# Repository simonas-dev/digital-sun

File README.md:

# Digital Sun

A cross-platform LED pattern system with real-time visualization and hardware control for Raspberry Pi.

## Overview

Digital Sun is a modular system for creating and displaying LED patterns:
- **Develop on macOS** with real-time OPENRNDR visualization
- **Deploy to Raspberry Pi** for physical LED strip control
- **Share core logic** between visualization and hardware

The build system automatically detects your platform and includes only relevant modules.

## Quick Start

### On macOS (Development & Visualization)
```bash
./gradlew build
./gradlew :sun-openrndr:run
```

### On Raspberry Pi (Hardware Control)
```bash
# Install rpi_ws281x library first (see BUILD.md)
./gradlew build
sudo ./target-rpi/build/bin/linuxArm64/releaseExecutable/target-rpi.kexe
```

## Project Structure

This project is organized into three modules:

### sun-core
Pure Kotlin/Java logic with no platform-specific dependencies.

**Contains:**
- `core/data/` - Data structures (Pixel, Stage)
- `core/shader/` - Shader algorithms and interfaces
- `core/noise/` - Noise generation interfaces

**Dependencies:** Kotlin stdlib, Kotlinx serialization, coroutines

**Purpose:** Reusable algorithms that can be used by any rendering backend.

### sun-openrndr
OPENRNDR visualization layer for desktop development and preview.

**Contains:**
- `openrndr/render/` - OPENRNDR-specific rendering
- `openrndr/noise/` - OPENRNDR noise adapter
- `openrndr/ui/` - GUI parameter controls
- Main application entry point

**Dependencies:** sun-core + OPENRNDR libraries

**Purpose:** Desktop application for developing and previewing shaders with a live GUI.

### target-rpi
Kotlin/Native LED strip control for Raspberry Pi via rpi_ws281x.

**Contains:**
- `rpi/` - Kotlin wrapper API for rpi_ws281x
- `nativeInterop/cinterop/` - C bindings for rpi_ws281x
- Example programs and animations

**Dependencies:** sun-core + rpi_ws281x (C library)

**Purpose:** Direct hardware control of WS281x LED strips on Raspberry Pi.

## Platform-Specific Builds

The build system automatically detects your platform:
- **macOS**: Builds `sun-core` + `sun-openrndr` (visualization)
- **Raspberry Pi** (Linux ARM): Builds `sun-core` + `target-rpi` (hardware)
- **Linux x86**: Builds all modules for testing

See [BUILD.md](BUILD.md) for detailed build instructions.

## Building

### macOS
```bash
./gradlew build                    # Builds sun-core + sun-openrndr
./gradlew :sun-openrndr:run        # Run visualization
./gradlew :sun-openrndr:shadowJar  # Create distributable
```

### Raspberry Pi
```bash
# Prerequisites: Install rpi_ws281x library (see BUILD.md)
./gradlew build                                        # Builds sun-core + target-rpi
./gradlew :target-rpi:linkReleaseExecutableLinuxArm64 # Build LED executable
sudo ./target-rpi/build/bin/linuxArm64/releaseExecutable/target-rpi.kexe
```

## Module Dependencies

```
┌──────────────────────┐          ┌──────────────────────┐
│    target-rpi        │          │    sun-openrndr      │
│  (Raspberry Pi HW)   │          │  (macOS/Linux viz)   │
│  Kotlin/Native       │          │  Kotlin/JVM          │
└──────────┬───────────┘          └──────────┬───────────┘
           │                                 │
           │         depends on              │
           └────────────┬────────────────────┘
                        │
                ┌───────▼────────┐
                │    sun-core    │
                │ (Shared logic) │
                │   Kotlin/JVM   │
                └────────────────┘
```

## Architecture

The core pattern logic is platform-agnostic. Different rendering backends provide:
1. **Noise generator implementation** - Adapts noise functions to the core interface
2. **Color output** - Converts core ColorValue to platform-specific format
3. **Rendering loop** - Drives patterns with time and parameters

This allows the same pattern logic to run on:
- **Desktop** (OPENRNDR) - Real-time preview with GUI controls
- **Raspberry Pi** (rpi_ws281x) - Physical LED strips via GPIO

## Documentation

- [BUILD.md](BUILD.md) - Detailed build instructions for all platforms
- [target-rpi/README.md](target-rpi/README.md) - LED hardware setup and API

## Requirements

- **All platforms**: JDK 17+, Gradle 8.14+ (included via wrapper)
- **Raspberry Pi only**: rpi_ws281x library (see BUILD.md for installation)

## License

MIT

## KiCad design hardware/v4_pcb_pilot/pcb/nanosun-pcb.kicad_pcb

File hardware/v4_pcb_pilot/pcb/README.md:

# nanosun-pcb

Carrier PCB for the SunsetLamp 150 mm circular LED pixel display. Holds 24 rows of WS2812B strip, provides power distribution and data routing.

**Status:** Sent to PCBWay for fabrication (2026-04-12).

---

## Board summary

| Parameter | Value |
|---|---|
| Shape | Circle, 165 mm diameter |
| Layers | 2 (F.Cu + B.Cu) |
| Thickness | 1.6 mm FR-4 |
| Surface finish | HASL lead-free |
| Solder mask / silk | Black / White |
| Copper weight | 1 oz |

## Components on board

| Ref | Part | Purpose |
|---|---|---|
| LED1–LED24 | WS2812B strip row footprints | 24 horizontal strip mounting positions (6–24 pixels each) |
| U1 | MP1584EN module | 12V → 5V buck regulator (powers RPi logic) |
| R1 | 330 R (THT) | Data line series resistor |
| C1, C2 | 100 uF electrolytic (THT) | Bulk decoupling on 12V rail |
| MH1–MH6 | M3 mounting holes | Mechanical mounting |
| 12V, GND, DIN, 5V | Wire solder pads | External connections |

## Power architecture

- Two vertical buses on F.Cu: **+12V** (right side, x ~228 mm) and **GND** (center-left, x ~148 mm).
- Each LED row has horizontal stubs from one side's pads to its bus. The opposite side relies on the physical strip bridging internally when soldered.
- Power traces: 1.0 mm width. Signal traces (DIN/DOUT): 0.2 mm.
- Worst-case voltage drop at full load (1.67 A): ~246 mV, ~4 C temp rise.

## Data chain

Serpentine pattern: LED1 → LED2 → ... → LED24. Odd rows route left-to-right, even rows right-to-left. DIN enters at a wire solder pad, passes through R1, then into LED1.

## DRC status (at time of fab submission)

- **0 real connectivity issues.** 48 DRC "unconnected items" are all false positives from strip-pad bridging (KiCad can't model the internal strip connection).
- 15 warnings: 10 silk-over-copper (auto-clipped by fab), 4 text height (cosmetic), 1 dangling stub (0.28 mm, harmless).
- 0 ERC violations. 0 schematic parity issues.

## Fabrication outputs

Generated gerbers, drill files, and zip are in `fab/`. These are the exact files uploaded to PCBWay.

## PCBWay order parameters

| Parameter | Value |
|---|---|
| Board type | Single pieces |
| Bounding box | 165 x 165 mm |
| Layers | 2 |
| Material | FR-4 TG130 |
| Thickness | 1.6 mm |
| Min track/spacing | 6/6 mil (design uses 0.2 mm) |
| Min hole | 0.3 mm (design uses 0.8 mm) |
| Solder mask | Black |
| Silkscreen | White |
| Surface finish | HASL lead-free |
| Copper weight | 1 oz |

## Order reference

| Item | Cost (USD) |
|---|---|
| 5x PCBs (165x165 mm, 2-layer) | $51.11 |
| Shipping (DHL) | $31.59 |
| Bank fee | $4.57 |
| Discount | -$5.00 |
| VAT | $17.28 |
| **Total** | **$99.55** |

Order W1045739ASG1, PCBWay via Hong Kong Yanghui, 2026-04-12. Unit cost $10.22/board before shipping.

## Assembly notes

When boards arrive, follow the procedure in the parent directory's `design-spec.md`:

1. Tin all strip pads on the PCB.
2. Cut WS2812B strips to row lengths per the pixel circle spec (section 3.2).
3. Align strips on pads, tack one end, then solder remaining pads.
4. Continuity-test each row's VCC/GND before powering.
5. First power-on with a 0.5 A current limit to catch shorts.

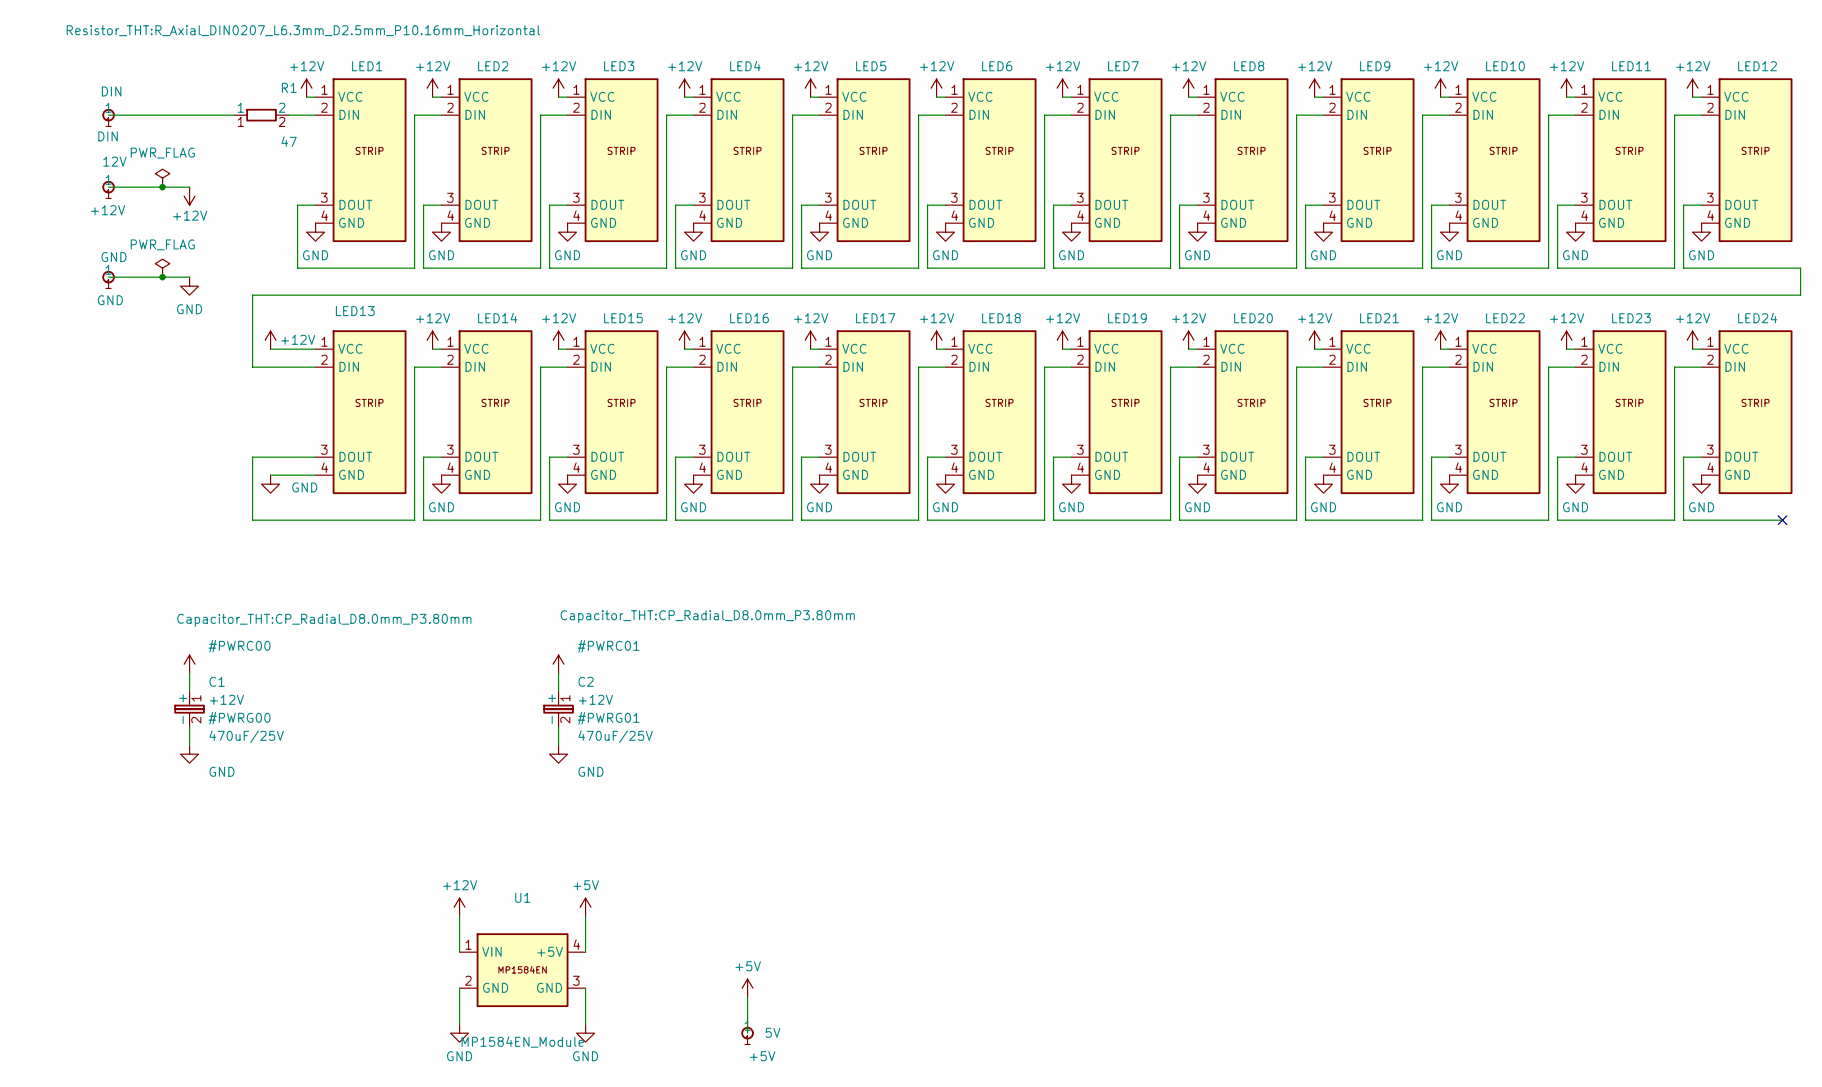
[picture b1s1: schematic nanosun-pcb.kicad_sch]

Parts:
5V: +5V; WireSolderPad_1
12V: +12V; WireSolderPad_1
C1, C2: 470uF/25V; CP_Radial_D8.0mm_P3.80mm
DIN: DIN; WireSolderPad_1
GND: GND; WireSolderPad_1
LED1, LED24: WS2812B_Strip; WS2812B_Row_06px_37_5mm
LED2, LED23: WS2812B_Strip; WS2812B_Row_12px_75mm
LED3, LED22: WS2812B_Strip; WS2812B_Row_14px_87_5mm
LED4, LED21: WS2812B_Strip; WS2812B_Row_16px_100mm
LED5, LED20: WS2812B_Strip; WS2812B_Row_18px_112_5mm
LED6, LED19: WS2812B_Strip; WS2812B_Row_20px_125mm
LED7, LED8, LED9, LED16, LED17, LED18: WS2812B_Strip; WS2812B_Row_22px_137_5mm
LED10, LED11, LED12, LED13, LED14, LED15: WS2812B_Strip; WS2812B_Row_24px_150mm
R1: 47; R_Axial_DIN0207_L6.3mm_D2.5mm_P10.16mm_Horizontal
U1: MP1584EN_Module

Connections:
+5V: 5V.1, U1.4 (+5V)
+12V: 12V.1, C1.1 (+), C2.1 (+), LED1.1 (VCC), LED2.1 (VCC), LED3.1 (VCC), LED4.1 (VCC), LED5.1 (VCC), LED6.1 (VCC), LED7.1 (VCC), LED8.1 (VCC), LED9.1 (VCC), LED10.1 (VCC), LED11.1 (VCC), LED12.1 (VCC), LED13.1 (VCC), LED14.1 (VCC), LED15.1 (VCC), LED16.1 (VCC), LED17.1 (VCC), LED18.1 (VCC), LED19.1 (VCC), LED20.1 (VCC), LED21.1 (VCC), LED22.1 (VCC), LED23.1 (VCC), LED24.1 (VCC), U1.1 (VIN)
GND: C1.2 (-), C2.2 (-), GND.1, LED1.4 (GND), LED2.4 (GND), LED3.4 (GND), LED4.4 (GND), LED5.4 (GND), LED6.4 (GND), LED7.4 (GND), LED8.4 (GND), LED9.4 (GND), LED10.4 (GND), LED11.4 (GND), LED12.4 (GND), LED13.4 (GND), LED14.4 (GND), LED15.4 (GND), LED16.4 (GND), LED17.4 (GND), LED18.4 (GND), LED19.4 (GND), LED20.4 (GND), LED21.4 (GND), LED22.4 (GND), LED23.4 (GND), LED24.4 (GND), U1.2 (GND), U1.3 (GND)
unnamed: DIN.1, R1.1
unnamed: LED1.2 (DIN), R1.2
unnamed: LED1.3 (DOUT), LED2.2 (DIN)
unnamed: LED2.3 (DOUT), LED3.2 (DIN)
unnamed: LED3.3 (DOUT), LED4.2 (DIN)
unnamed: LED4.3 (DOUT), LED5.2 (DIN)
unnamed: LED5.3 (DOUT), LED6.2 (DIN)
unnamed: LED6.3 (DOUT), LED7.2 (DIN)
unnamed: LED7.3 (DOUT), LED8.2 (DIN)
unnamed: LED8.3 (DOUT), LED9.2 (DIN)
unnamed: LED9.3 (DOUT), LED10.2 (DIN)
unnamed: LED10.3 (DOUT), LED11.2 (DIN)
unnamed: LED11.3 (DOUT), LED12.2 (DIN)
unnamed: LED12.3 (DOUT), LED13.2 (DIN)
unnamed: LED13.3 (DOUT), LED14.2 (DIN)
unnamed: LED14.3 (DOUT), LED15.2 (DIN)
unnamed: LED15.3 (DOUT), LED16.2 (DIN)
unnamed: LED16.3 (DOUT), LED17.2 (DIN)
unnamed: LED17.3 (DOUT), LED18.2 (DIN)
unnamed: LED18.3 (DOUT), LED19.2 (DIN)
unnamed: LED19.3 (DOUT), LED20.2 (DIN)
unnamed: LED20.3 (DOUT), LED21.2 (DIN)
unnamed: LED21.3 (DOUT), LED22.2 (DIN)
unnamed: LED22.3 (DOUT), LED23.2 (DIN)
unnamed: LED23.3 (DOUT), LED24.2 (DIN)

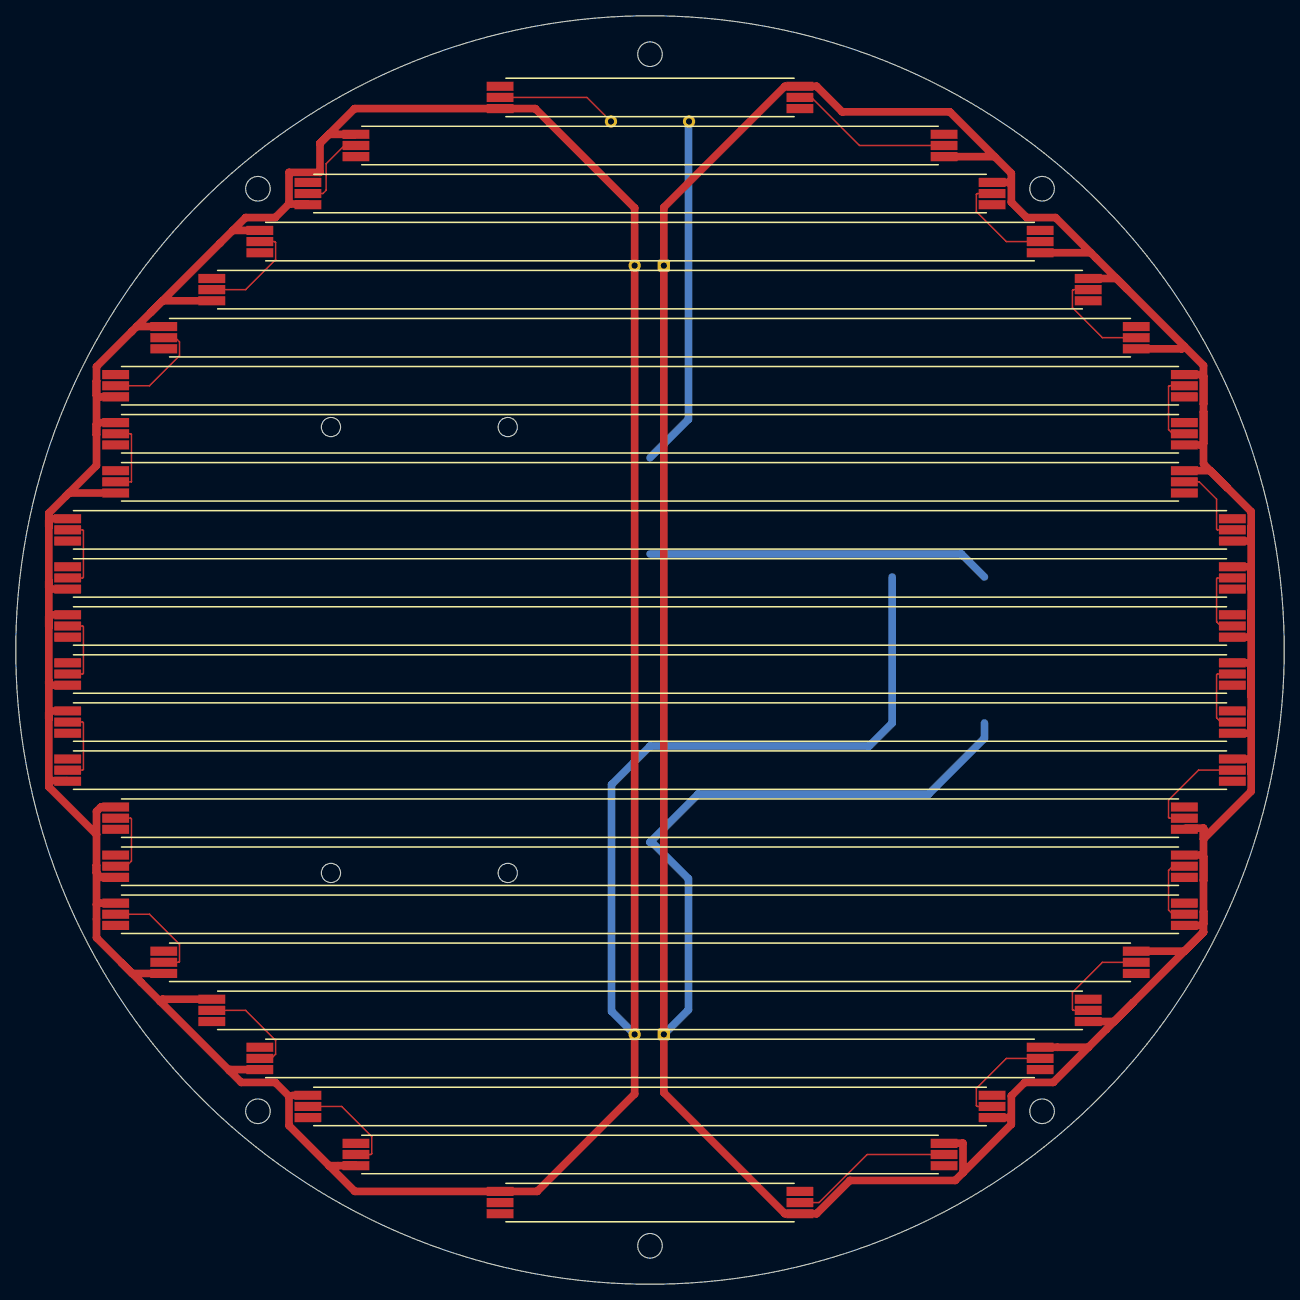
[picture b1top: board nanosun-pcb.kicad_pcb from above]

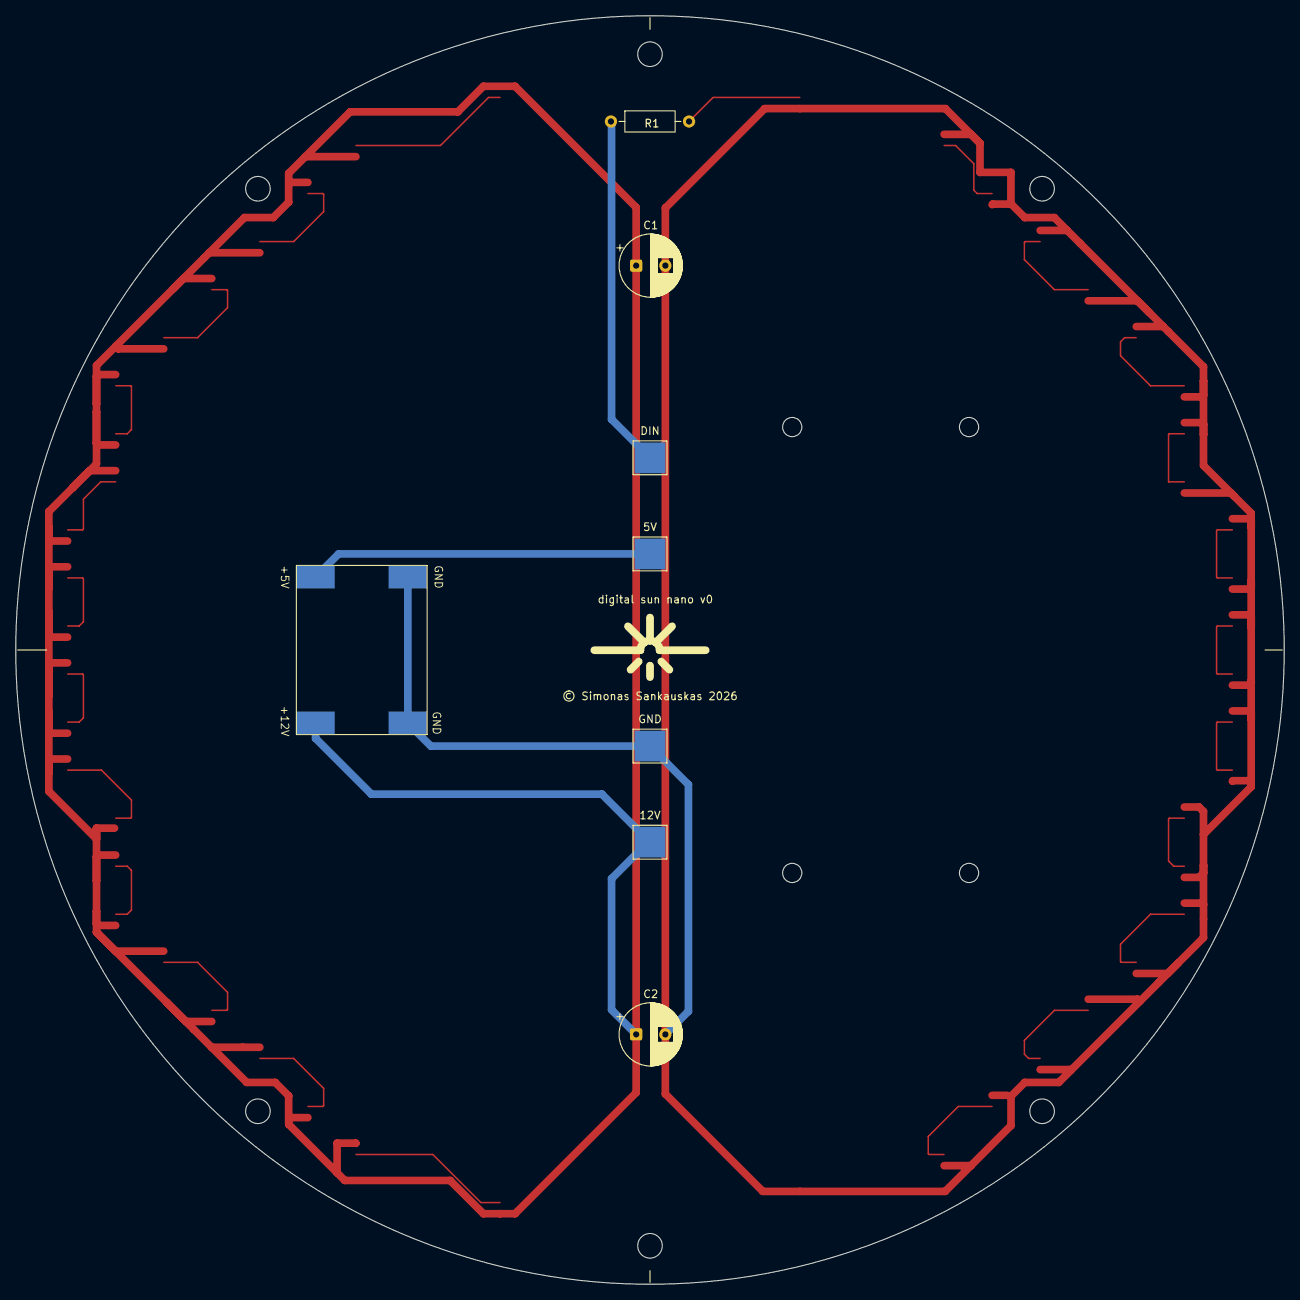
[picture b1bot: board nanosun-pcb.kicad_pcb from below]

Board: 2 copper layers, 165.0 x 165.0 mm, 42 parts (8 on the bottom side), 28 nets.

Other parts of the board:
MH1, MH2, MH3, MH4, MH5, MH6: MountingHole_3.2mm_M3_DIN965
RPI_MH7, RPI_MH8, RPI_MH9, RPI_MH10: MountingHole_2.5mm

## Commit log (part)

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2025-10-15 good shit
2025-10-16 fix structure
2025-10-16 set params
2025-10-16 creatre modules
2025-10-16 fill modules
2025-10-16 cleanup
2025-10-16 gradle cleanup
2025-10-16 add rpi as target
2025-10-16 replace multiplatform to jvm
2025-10-16 Revert "replace multiplatform to jvm"
    This reverts commit 7e04d2d469eecc9a91c4e7634737069fa6f3f48a.
2025-10-16 fix rpi target
2025-10-16 update jvm
2025-10-16 implement anim from core to rpi target
2025-10-16 tweaks for rpi target
2025-10-17 remote deployment to RPI. Shutdown via interrupt is not clean.
2025-10-17 kill remote process gracefully cleanup
2025-10-17 deployment shutdown fixed
2025-10-17 tweaks
2025-10-19 new hue algo
2025-10-23 warm algo
2025-10-26 labas
2025-10-31 new stage
2025-10-31 best engineering
2025-10-31 fix run script
2025-10-31 new looks
2025-11-18 move to spi pin
2025-11-18 increase redness in shader
2025-11-18 fix vibes in deploy script
2025-11-18 make run script execable
2025-11-18 setup autostart
2026-03-13 change d pin
2026-03-13 change deploy address
2026-03-26 Stages as Build Arguments
2026-04-05 flashing & backup script
2026-04-05 fix interative UI
2026-04-05 plan and utils
2026-04-08 generative shaders
2026-04-08 move the hardware specs for the v3 to it's dir
2026-04-08 kicad pcb schematic no ERC errors
2026-04-08 fix pcb design issues
2026-04-08 pcb diagram
2026-04-08 manually adjusted the pcb
2026-04-08 circle pcb with touchups
2026-04-08 DRC fixes
2026-04-12 final checklists
2026-04-12 fix pixel silkscreen
2026-04-12 pretty lines
2026-04-12 sent pcb for manufacturing
2026-04-12 restructure the hw dir
2026-04-17 fix mixup between v1 and v2 versions
2026-04-17 artisinal handwork changes
2026-04-17 improved TUI
2026-04-17 make more sense
2026-04-17 dope TUI

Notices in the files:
hardware/v4_pcb_pilot/pcb/nanosun-pcb.kicad_pcb:
© Simonas Sankauskas 2026
